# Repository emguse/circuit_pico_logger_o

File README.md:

# pico_logger_o

A device to record the rate of change of differential pressure using an OMRON D6F sensor, built with Raspberry Pi pico and CircuitPython.

A personal project of `emguse`, a port of the [emguse/diff_press_logger_o](https://github.com/emguse/diff_press_logger_o) project to a microcontroller.

# Notes.
- The PB-0009-A PCB board has three different power input methods, but there is no diode protection between each of them.
- Always use only one type of power input.
- If you are using the Pico's USB to supply power, it will not be able to provide power for the printer. Do not connect the printer or turn off the setting to use it.

# Features
- Time recording by RTC
- Event recording (CSV file)
- Event recording (print to thermal printer)
- Pre- and post-event recording is possible. (Number of seconds can be set.)
- Trigger detection using differences from past measurements
- Threshold change button
- Reset button

# What you need

## What to buy
- Rapberry Pi pico RP2040
- OMRON D6F-PH0505 Differential pressure sensor
- special harness with GHR-04V-S used for D6F-PH0505
- Adafruit DS3231 Precision RTC-STEMMA QT(Product ID: 5188)
- STEMMA QT / Qwiic JST SH 4-pin Cable - 100mm Long(Product ID: 4210)
- Adafruit Micro SD SPI or SDIO Card Breakout Board(Product ID: 4682)
- Thermal printer DP-EH600
- 5V 2A power supply (2.1mm DC barrel plug)

## Printed circuit board
- PB-0009-A PCB board
- 2.1mm DC barrel jack
- B2B-XH-AM(LF)(SN) JST
- B3B-XH-AM(LF)(SN) JST
- B8B-XH-AM(LF)(SN) JST
- 2.2k Ohm Resistor_SMD:R_0603_1608Metric
- 3.3k Ohm Resistor_SMD:R_0603_1608Metric
- 10k Ohm Resistor_SMD:R_0603_1608Metric
- PinHeader_1x02_P2.54mm_Vertical
- SW_Push_1P1T_NO_6x6mm
- Buzzer_12x9.5RM7.6(self-excited)
- 2SC2712 Toshiba
- BM04B-SRSS-TB_1x04-1MP_P1.00mm_Vertical JST SH

## airtight container
- enclosure_body.stl
- enclosure_lid.stl
- enclosure_sensor_fixture.stl
- Bit Insert M3x4.5xL10.0
- M3x16mm cap screws
- O-ring d84.4mm-D90.6mm-W3.1mm(G-85)
- Cable gland M10x13mm d6mm (ex. RM10L-6B takachi)
- 6mmx4mm Tube

# Usage

1. Connect Pico to your PC in Boot mode and transfer the latest `.UF2` file for Pico.
1. Transfer the modules listed in `Requirement` from the Circuitpython bundle to the `lib` folder.
1. Rename the `pico_diff_p_o.py` file to `code.py` after transferring the files in this repository.

# Requirement
- adafruit_bus_device.i2c_device
- adafruit_register
- adafruit_thermal_printer
- adafruit_ds3231

# Author

- Author: emguse

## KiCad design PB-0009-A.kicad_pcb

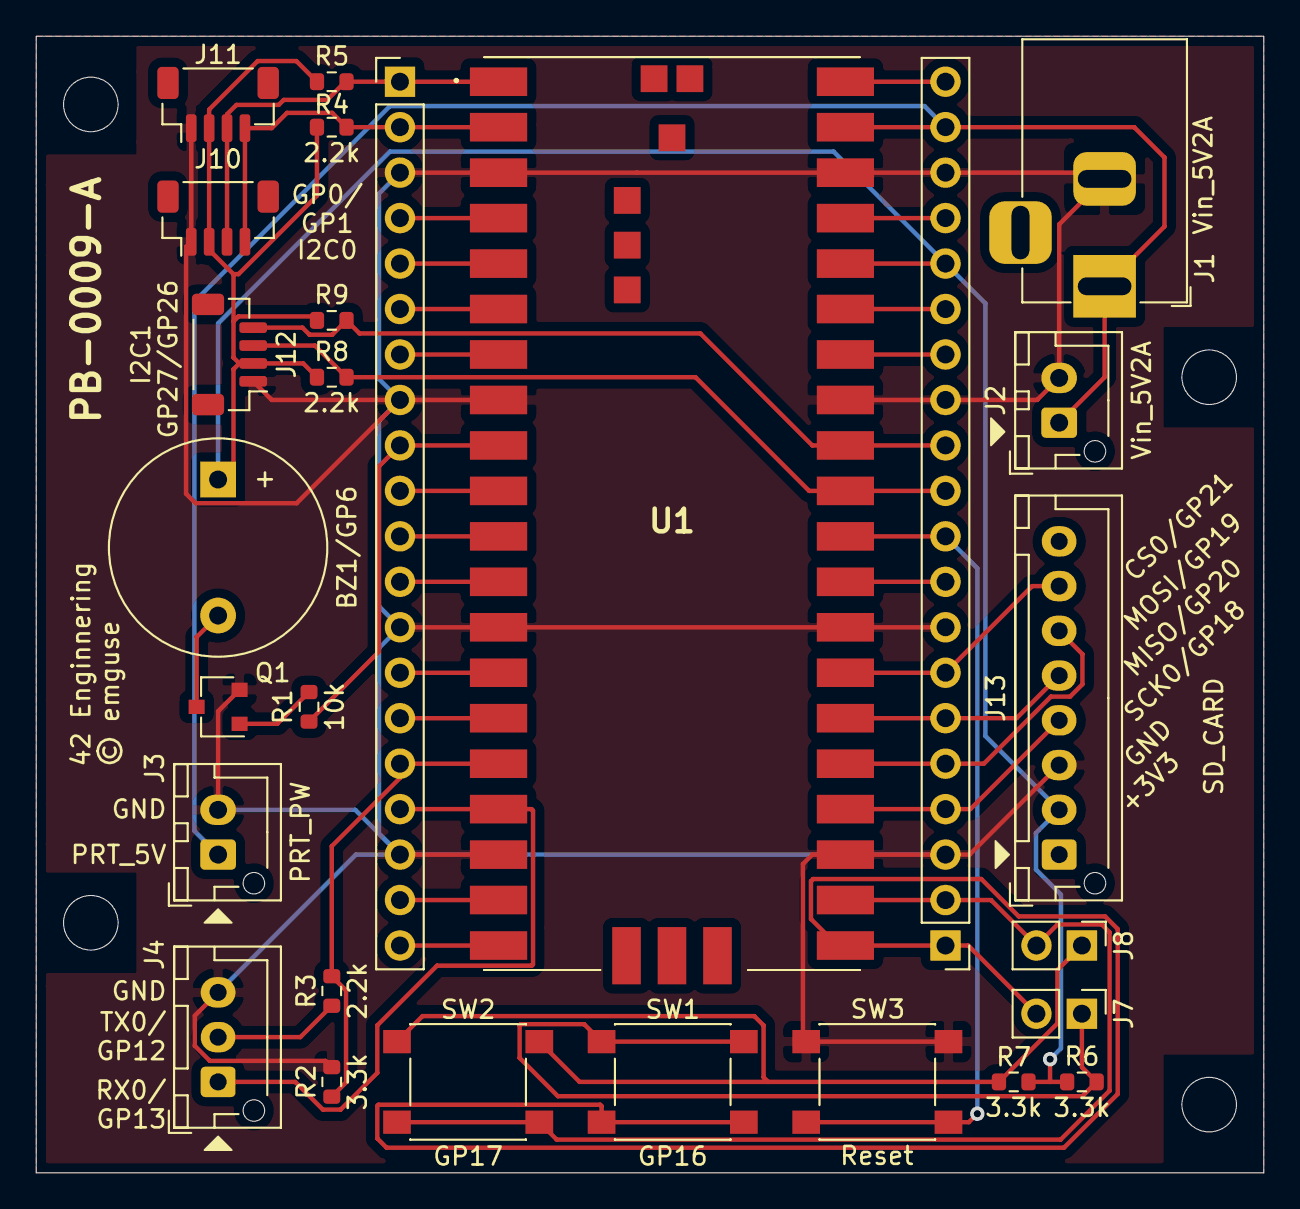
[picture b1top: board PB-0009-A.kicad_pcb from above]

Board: 2 copper layers, 68.6 x 63.5 mm, 27 parts (0 on the bottom side), 38 nets.

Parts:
BZ1/GP6: Buzzer; Buzzer_12x9.5RM7.6
J1: Vin_5V2A; BarrelJack_Horizontal
J2: Vin_5V2A; JST_XH_B2B-XH-AM_1x02_P2.50mm_Vertical
J3: PRT_PW; JST_XH_B2B-XH-AM_1x02_P2.50mm_Vertical
J4: Conn_01x03; JST_XH_B3B-XH-AM_1x03_P2.50mm_Vertical
J5, J9: Conn_01x20_Female; PinHeader_1x20_P2.54mm_Vertical
J7: TH_UP; PinHeader_1x02_P2.54mm_Vertical
J8: TH_DOWN; PinHeader_1x02_P2.54mm_Vertical
J10, J11: I2C0; JST_SH_BM04B-SRSS-TB_1x04-1MP_P1.00mm_Vertical
J12: I2C1; JST_SH_BM04B-SRSS-TB_1x04-1MP_P1.00mm_Vertical
J13: SD_CARD; JST_XH_B8B-XH-AM_1x08_P2.50mm_Vertical
Q1: Q_NPN_BEC; SC-59
R1: 10k; R_0603_1608Metric
R2, R6, R7: 3.3k; R_0603_1608Metric
R3, R4, R5, R8, R9: 2.2k; R_0603_1608Metric
SW1: GP16; SW_Push_1P1T_NO_6x6mm_H9.5mm
SW2: GP17; SW_Push_1P1T_NO_6x6mm_H9.5mm
SW3: Reset; SW_Push_1P1T_NO_6x6mm_H9.5mm
U1: PICO

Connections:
+3V3: BZ1/GP6.1, J9.16, J10.2, J11.2, J12.2, J13.2, R4.1, R5.1, R6.1, R7.1, R8.1, R9.1, U1.36
/BUZZ_SIG: J5.9, R1.2, U1.9
/CS0: J9.7, J13.7, U1.27
/DI0_MISO: J9.6, J13.5, U1.26
/DO0_MOSI: J9.5, J13.6, U1.25
/PRT_5V: J1.1, J2.1, J3.1, J9.19, U1.39
/RUN: J9.10, SW3.1, U1.30
/RX0: J4.1, J5.17, U1.17
/SCK0: J9.4, J13.4, U1.24
/SCL0: J5.2, J10.4, J11.4, R4.2, U1.2
/SCL1: J9.12, J12.4, R9.2, U1.32
/SDA0: J5.1, J10.3, J11.3, R5.2, U1.1
/SDA1: J9.11, J12.3, R8.2, U1.31
/TH_DOWN: J8.2, J9.2, SW2.2, U1.22
/TH_UP: J7.2, J9.1, SW1.2, U1.21
/TX0: J5.16, R2.1, R3.2, U1.16
GND: J1.2, J2.2, J3.2, J4.3, J5.3, J5.8, J5.13, J5.18, J9.3, J9.8, J9.13, J9.18, J10.1, J11.1, J12.1, J13.3, Q1.2, R2.2, SW3.2, U1.3, U1.8, U1.13, U1.18, U1.23, U1.28, U1.33, U1.38
unnamed: BZ1/GP6.2, Q1.3
unnamed: J4.2, R3.1
unnamed: J5.4, U1.4
unnamed: J5.5, U1.5
unnamed: J5.6, U1.6
unnamed: J5.7, U1.7
unnamed: J5.10, U1.10
unnamed: J5.11, U1.11
unnamed: J5.12, U1.12
unnamed: J5.14, U1.14
unnamed: J5.15, U1.15
unnamed: J5.19, U1.19
unnamed: J5.20, U1.20
unnamed: J9.9, U1.29
unnamed: J9.14, U1.34
unnamed: J9.15, U1.35
unnamed: J9.17, U1.37
unnamed: J9.20, U1.40
unnamed: J7.1, R6.2, SW1.1
unnamed: J8.1, R7.2, SW2.1
unnamed: Q1.1, R1.1

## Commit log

2022-01-10 add image
2022-01-11 Linked to the sibling project
2022-01-12 add comment
2022-01-13 Added blinking onboard LED to check for life and death
2022-01-21 Addition of precautions
2022-01-28 Improved log accuracy by rearranging the processing order. Improvement of the timestamp system. Bug fixes.
2022-01-29 Separate timestamp processing into getting and printing.
2022-02-05 Fixed queue handling
2022-02-13 test 7seg4digit
2022-02-14 Fix comment-out deletion errors
2022-02-21 rename files

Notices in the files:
PB-0009-A.kicad_pcb:
© emguse
